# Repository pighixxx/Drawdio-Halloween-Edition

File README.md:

# Drawdio: Halloween Edition

Designed for our SMD soldering workshop at Maker Faire Bilbao 2017, this version of Drawdio celebrates Halloween with a Day of the Dead Mexican skull design.

Drawdio. Original design by Jay Silver. 
License: Creative CommonsAttribution-ShareAlike 3.0 (CC BY-SA 3.0)

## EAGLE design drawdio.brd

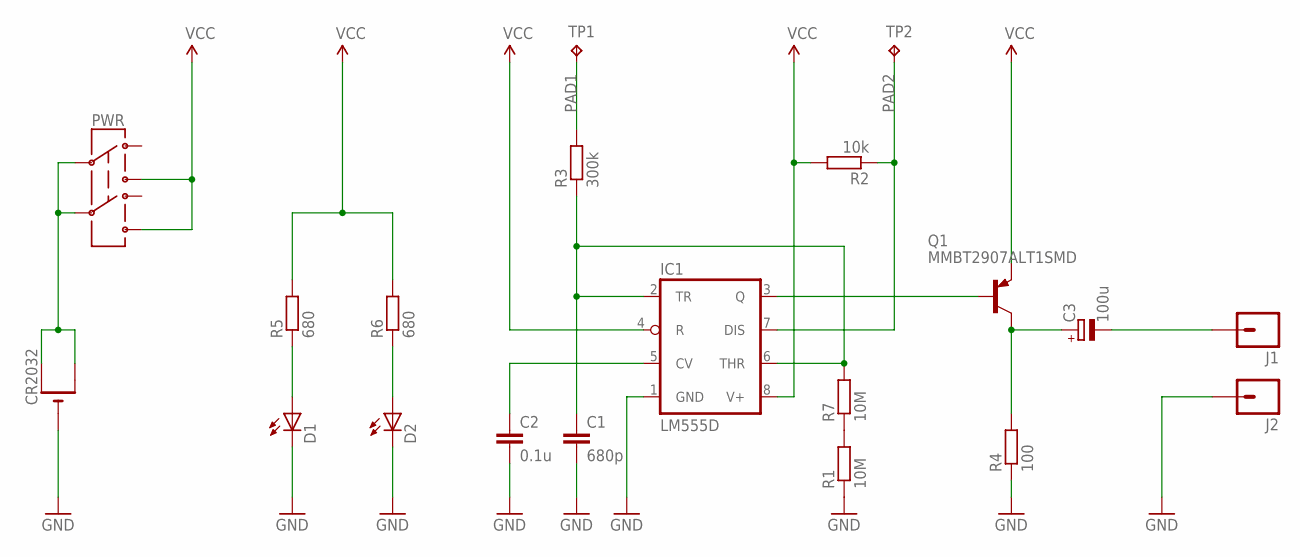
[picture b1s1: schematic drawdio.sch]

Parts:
C1: 680p; C1206K
C2: 0.1u; C1206K
C3: 100u; 153CLV-0605
CR2032: CR2032THM; CR2032-THRU
D1, D2: LED-1206; C1206
IC1: LM555D; SO08
J1, J2: M01NOSILK-KIT; 1X01NS-KIT
PWR: SWITCH-DPDTOS; OS
Q1: MMBT2907ALT1SMD; SOT23-BEC
R1, R7: 10M; R1206W
R2: 10k; R1206W
R3: 300k; R1206W
R4: 100; R1206W
R5, R6: 680; R1206W
TP1, TP2: TPB2,54; B2,54

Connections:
GND: C1.2, C2.2, CR2032.-, D1.C, D2.C, IC1.1 (GND), J2.1, R1.1, R4.1
unnamed: C2.1, IC1.5 (CV)
unnamed: C1.1, IC1.2 (TR), IC1.6 (THR), R3.1, R7.2
unnamed: IC1.3 (Q), Q1.B
unnamed: C3.+, Q1.C, R4.2
unnamed: D1.A, R5.1
unnamed: C3.-, J1.1
unnamed: D2.A, R6.1
unnamed: CR2032.+1 (+), CR2032.+2 (+1), PWR.2, PWR.5
unnamed: R1.2, R7.1
PAD1: R3.2, TP1.TP
PAD2: IC1.7 (DIS), R2.1, TP2.TP
VCC: IC1.4 (R), IC1.8 (V+), PWR.3, PWR.6, Q1.E, R2.2, R5.2, R6.2

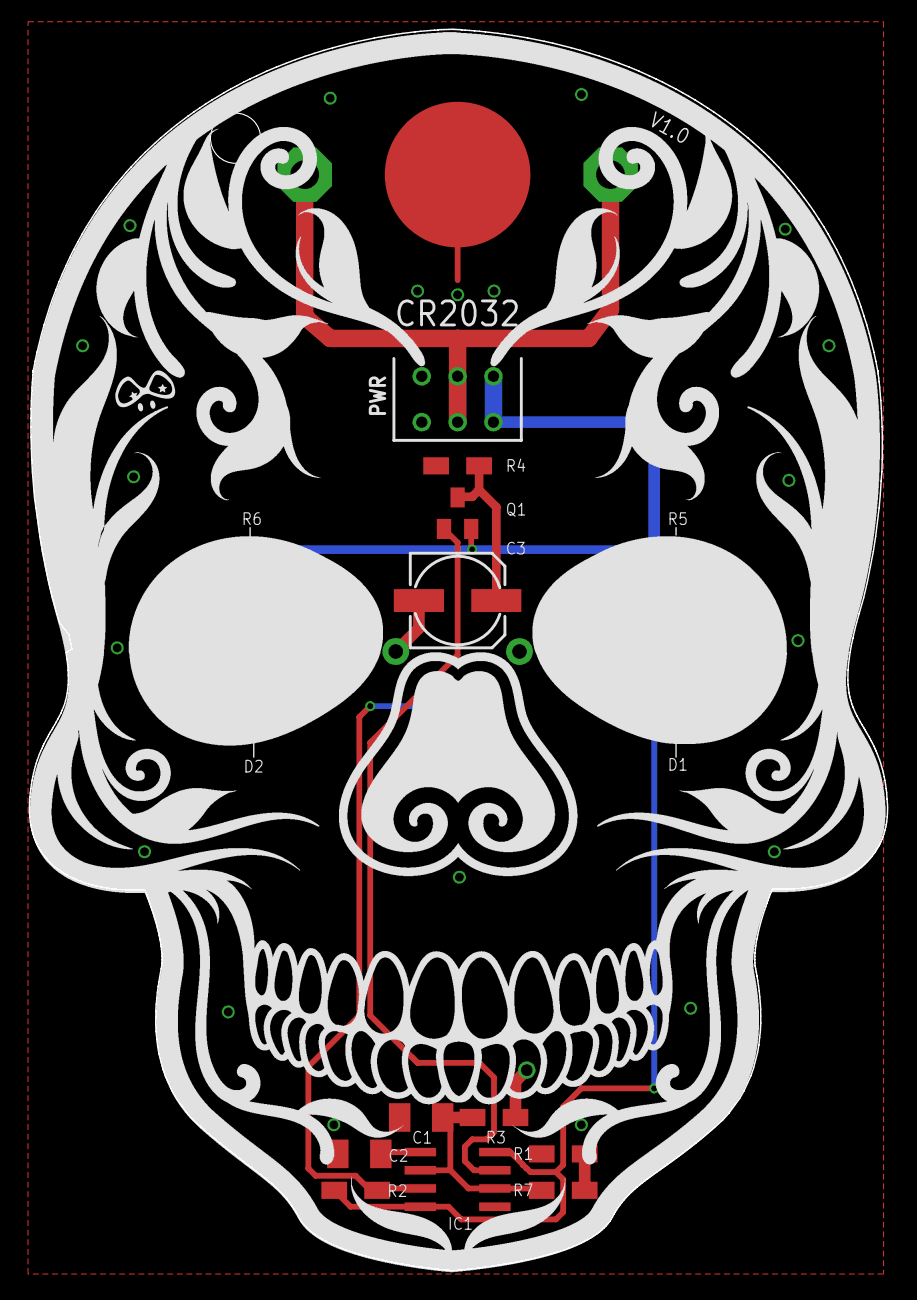
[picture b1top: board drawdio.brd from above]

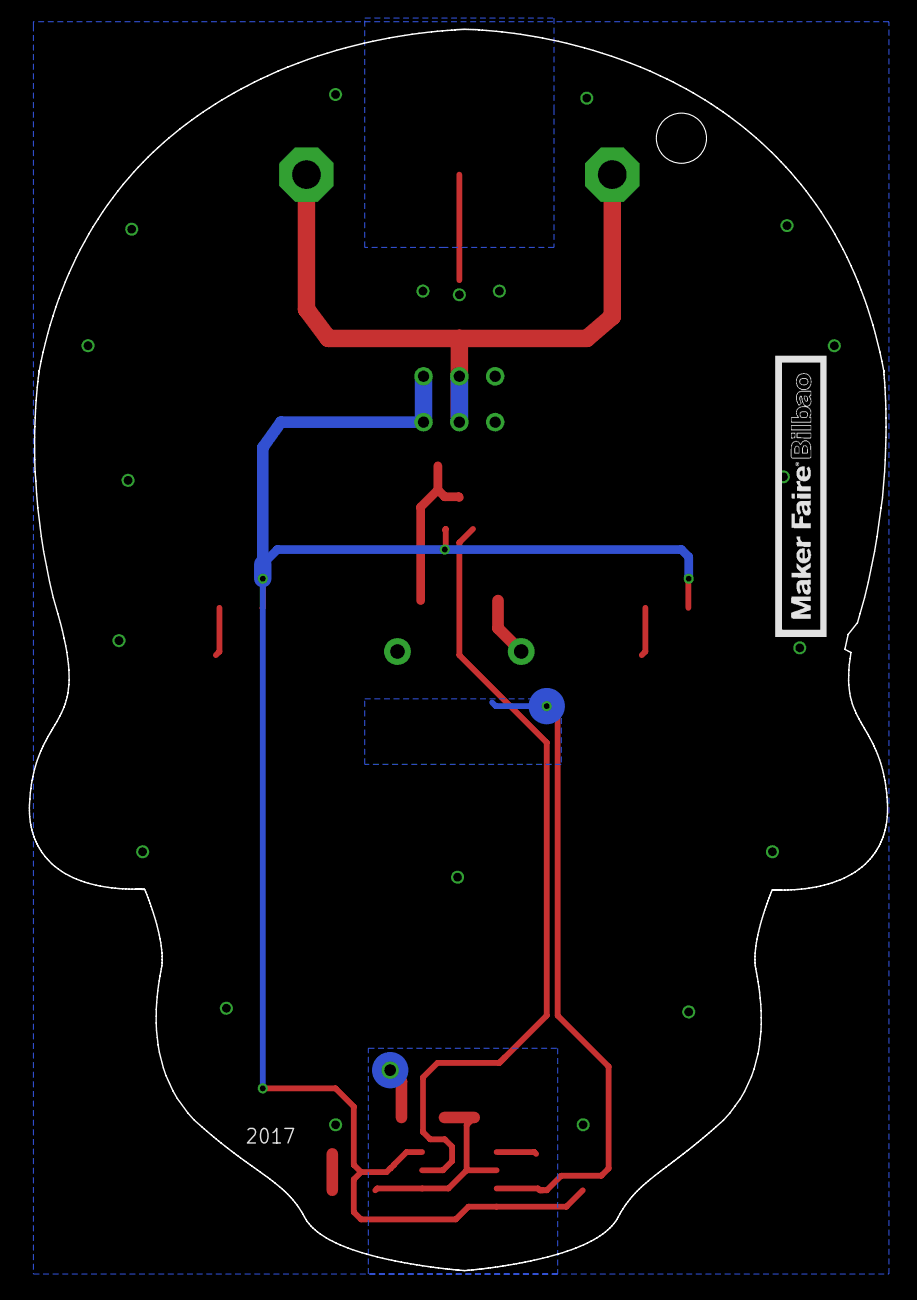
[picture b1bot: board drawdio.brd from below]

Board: 2 copper layers, 59.9 x 86.6 mm, 24 parts (3 on the bottom side), 13 nets.

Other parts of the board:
U$1: PIGHIXXX_LOGO
U$2: SKULL_TOP
U$3: SKULL_BOTTOM
U$4: MFBILBAO

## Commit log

2017-10-30 Add files
2017-10-30 Add media, BOM and modify README
2017-10-30 Modify README

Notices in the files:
parts and their libraries:
SparkFun-Electromechanical: Licensing: Creative Commons ShareAlike 4.0 International - https://creativecommons.org/licenses/by-sa/4.0
